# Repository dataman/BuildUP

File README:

While teaching buildups for SynShop, the Las vegas Hackerspace, I noticed that it's really hard to figure out when all students are completed with a step.  BuildUP is an experimental Student-Teacher communication device that the students activate at the start of step.  A LED will blink slowly at first, then more rapidly as time goes on.  This provides feedback to the instructor on which students are having problems with a particular step.

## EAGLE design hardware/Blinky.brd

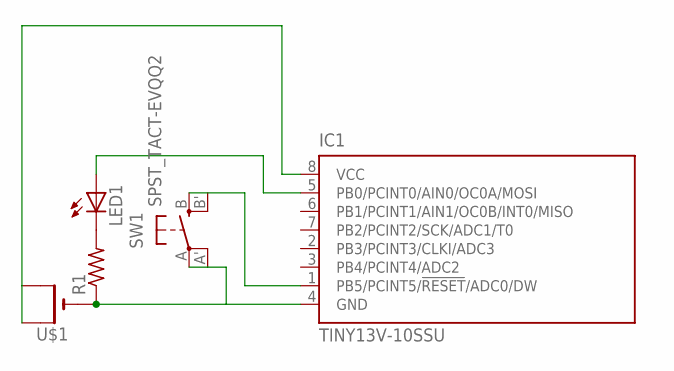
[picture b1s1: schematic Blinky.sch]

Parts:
IC1: TINY13V-10SSU; 8S1; MPN ATTINY13V-10SSU
LED1: LEDCHIPLED_1206; CHIPLED_1206
R1: R-US_M1206; M1206
SW1: SPST_TACT-EVQQ2; EVQ-Q2
U$1: CR1220SMT; CR1220-SMD

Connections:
unnamed: IC1.4 (GND), R1.1, SW1.A, SW1.A' (P1), U$1.-
unnamed: IC1.8 (VCC), U$1.+$1 (+), U$1.+$2 (+1)
unnamed: IC1.1 (PB5/PCINT5/!RESET!/ADC0/DW), SW1.B (S)
unnamed: LED1.C, R1.2
unnamed: IC1.5 (PB0/PCINT0/AIN0/OC0A/MOSI), LED1.A

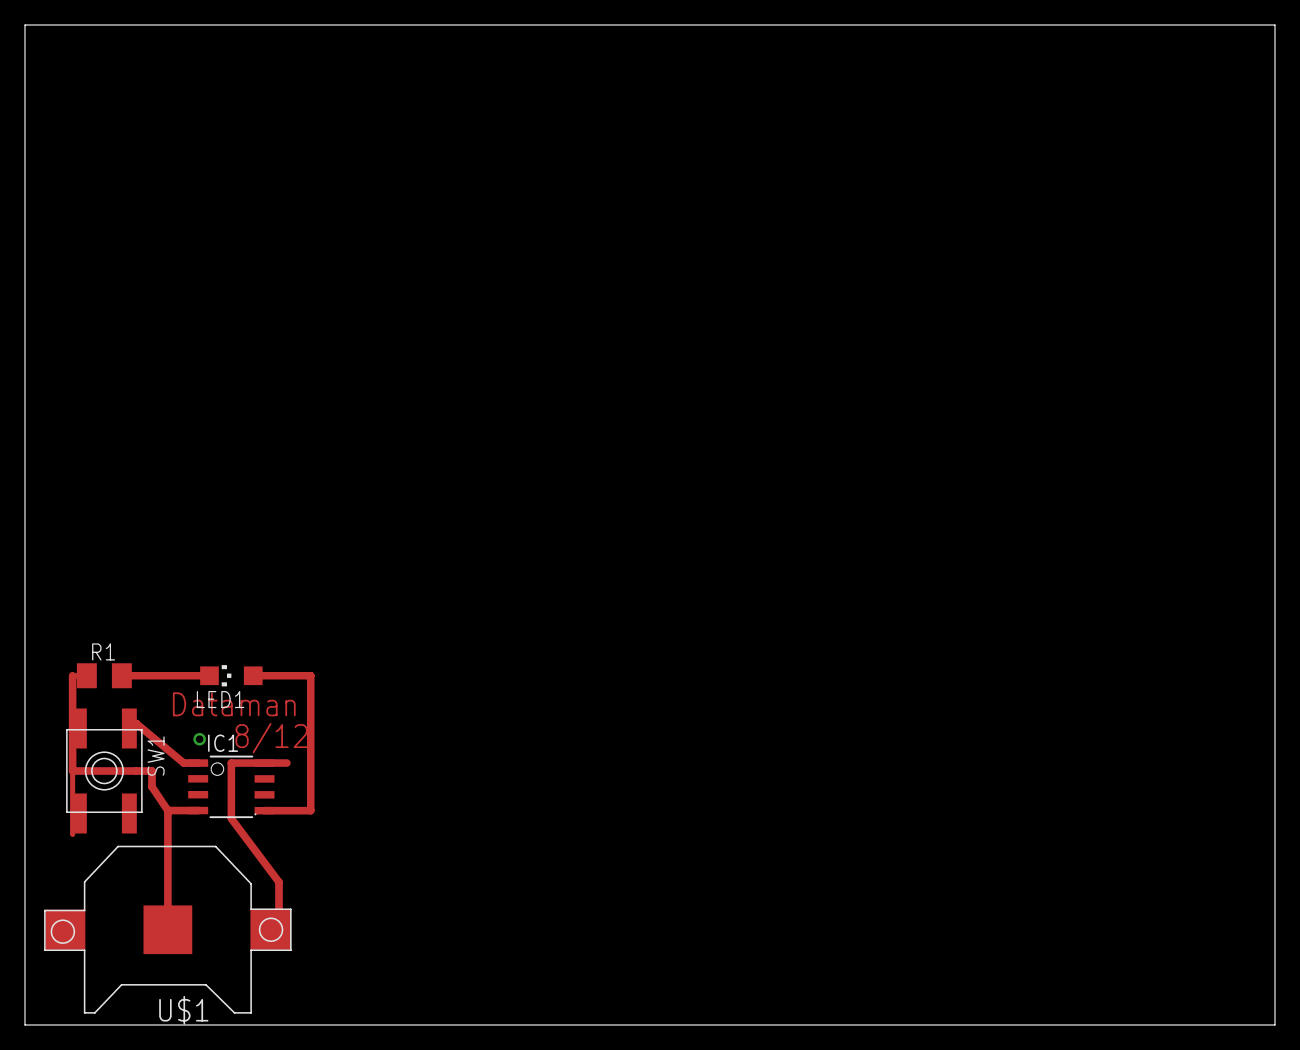
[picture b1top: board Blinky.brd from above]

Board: 2 copper layers, 100.0 x 80.0 mm, 5 parts (0 on the bottom side), 5 nets.

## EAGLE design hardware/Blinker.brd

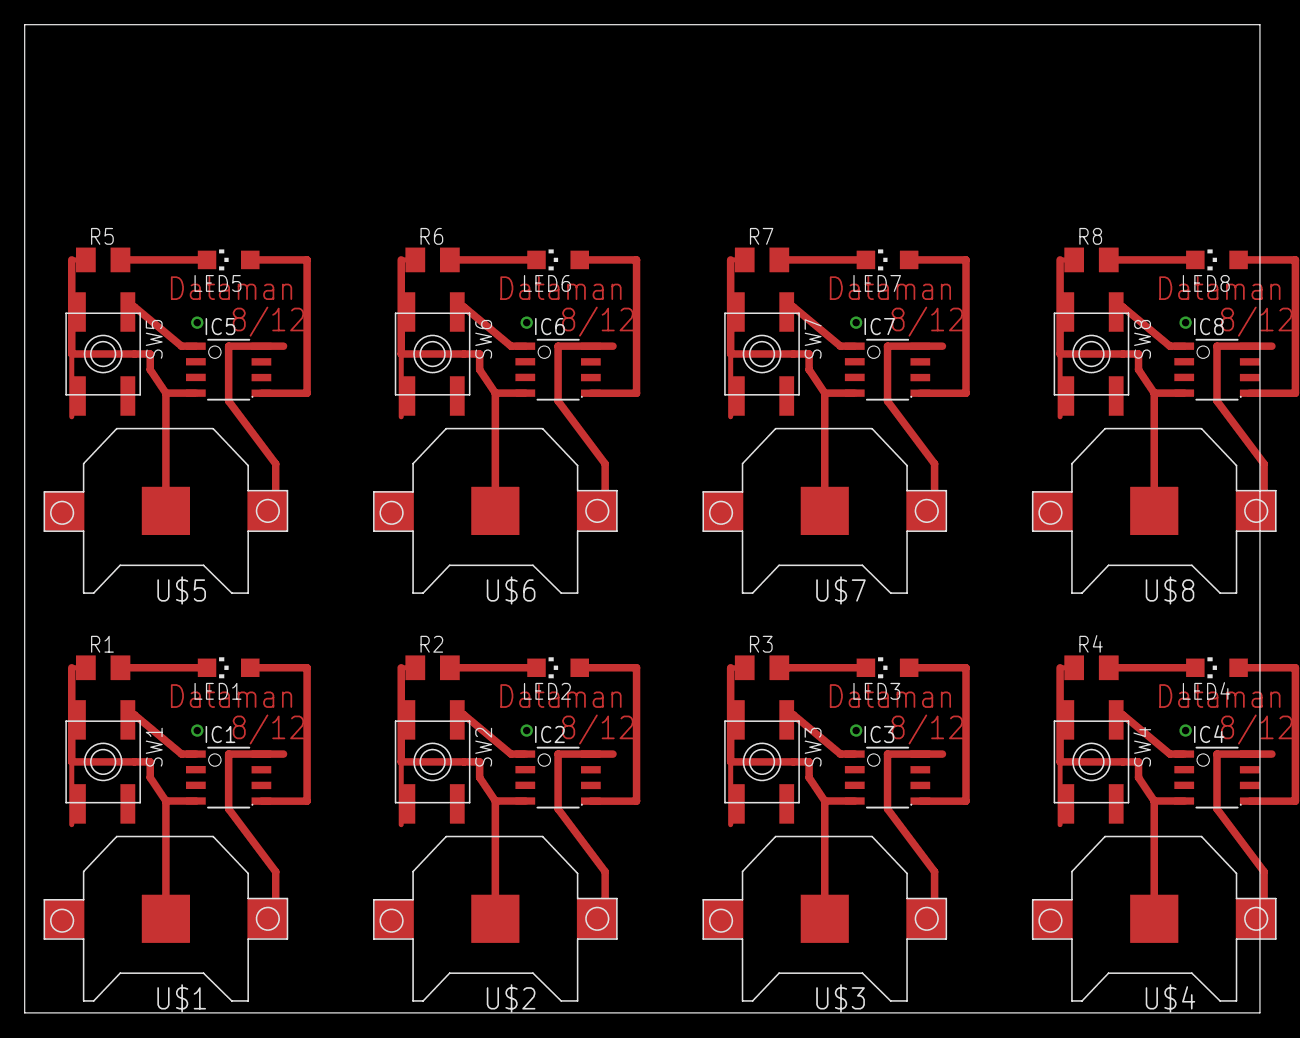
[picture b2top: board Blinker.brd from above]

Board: 2 copper layers, 100.0 x 80.0 mm, 40 parts (0 on the bottom side), 40 nets.

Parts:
IC1, IC2, IC3, IC4, IC5, IC6, IC7, IC8: TINY13V-10SSU; 8S1
LED1, LED2, LED3, LED4, LED5, LED6, LED7, LED8: CHIPLED_1206
R1, R2, R3, R4, R5, R6, R7, R8: M1206
SW1, SW2, SW3, SW4, SW5, SW6, SW7, SW8: SPST_TACT-EVQQ2; EVQ-Q2
U$1, U$2, U$3, U$4, U$5, U$6, U$7, U$8: CR1220-SMD

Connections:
unnamed: IC1.4, R1.1, SW1.A, SW1.A', U$1.-
unnamed: IC1.8, U$1.+$1, U$1.+$2
unnamed: IC1.1, SW1.B
unnamed: LED1.C, R1.2
unnamed: IC1.5, LED1.A
unnamed: IC2.4, R2.1, SW2.A, SW2.A', U$2.-
unnamed: IC2.8, U$2.+$1, U$2.+$2
unnamed: IC2.1, SW2.B
unnamed: LED2.C, R2.2
unnamed: IC2.5, LED2.A
unnamed: IC3.4, R3.1, SW3.A, SW3.A', U$3.-
unnamed: IC3.8, U$3.+$1, U$3.+$2
unnamed: IC3.1, SW3.B
unnamed: LED3.C, R3.2
unnamed: IC3.5, LED3.A
unnamed: IC4.4, R4.1, SW4.A, SW4.A', U$4.-
unnamed: IC4.8, U$4.+$1, U$4.+$2
unnamed: IC4.1, SW4.B
unnamed: LED4.C, R4.2
unnamed: IC4.5, LED4.A
unnamed: IC5.4, R5.1, SW5.A, SW5.A', U$5.-
unnamed: IC5.8, U$5.+$1, U$5.+$2
unnamed: IC5.1, SW5.B
unnamed: LED5.C, R5.2
unnamed: IC5.5, LED5.A
unnamed: IC6.4, R6.1, SW6.A, SW6.A', U$6.-
unnamed: IC6.8, U$6.+$1, U$6.+$2
unnamed: IC6.1, SW6.B
unnamed: LED6.C, R6.2
unnamed: IC6.5, LED6.A
unnamed: IC7.4, R7.1, SW7.A, SW7.A', U$7.-
unnamed: IC7.8, U$7.+$1, U$7.+$2
unnamed: IC7.1, SW7.B
unnamed: LED7.C, R7.2
unnamed: IC7.5, LED7.A
unnamed: IC8.4, R8.1, SW8.A, SW8.A', U$8.-
unnamed: IC8.8, U$8.+$1, U$8.+$2
unnamed: IC8.1, SW8.B
unnamed: LED8.C, R8.2
unnamed: IC8.5, LED8.A

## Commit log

2012-08-19 Initial Version
2012-08-20 Tuning for 5 minutes
2012-08-20 Tuning, Now 7 Minutes
    Starts at 3 second delay, steps down to 1/2 second delay
2012-08-20 debug, code syntax.
2012-08-21 tweaking time
2012-08-23 Final Version
